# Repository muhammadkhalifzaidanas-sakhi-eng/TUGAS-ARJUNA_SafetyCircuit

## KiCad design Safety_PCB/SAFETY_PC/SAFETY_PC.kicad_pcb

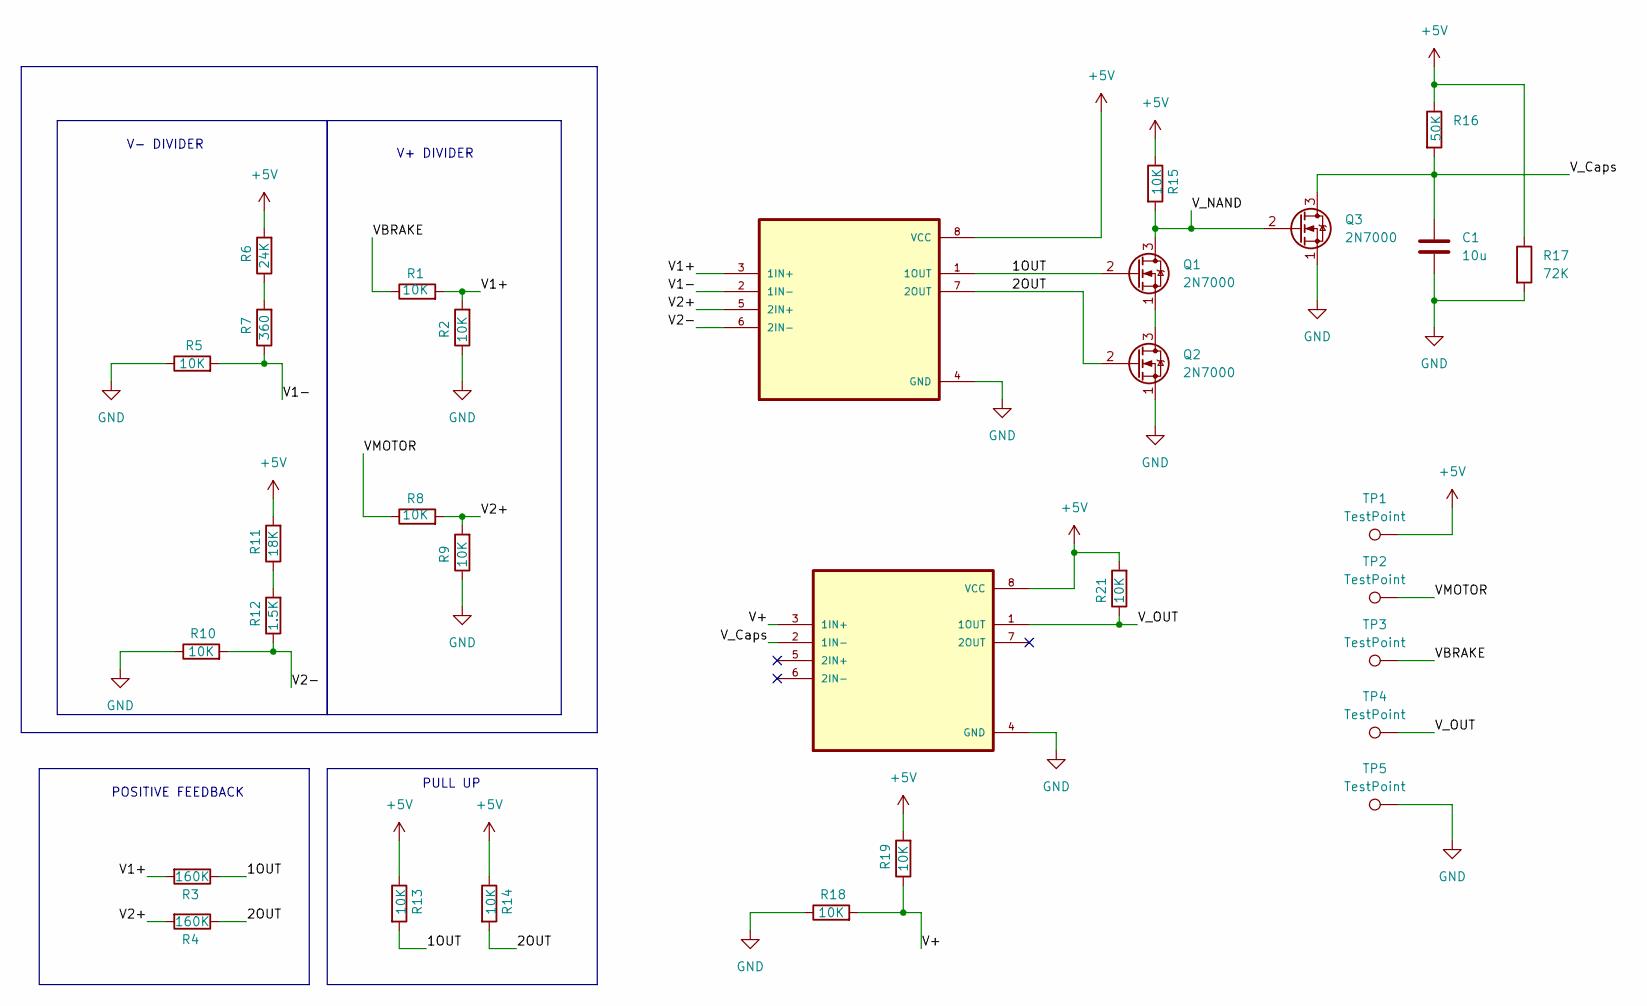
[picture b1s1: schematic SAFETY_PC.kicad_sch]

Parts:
C1: 10u; C_0603_1608Metric
Q1, Q2, Q3: 2N7000; TO-92_Inline_Horizontal1
R1, R2, R5, R8, R9, R10, R13, R14, R15, R18, R19, R21: 10K; R_0603_1608Metric
R3, R4: 160K; R_0603_1608Metric
R6: 24K; R_0603_1608Metric
R7: 360; R_0603_1608Metric
R11: 18K; R_0603_1608Metric
R12: 1.5K; R_0603_1608Metric
R16: 50K; R_0603_1608Metric
R17: 72K; R_0603_1608Metric
TP1, TP2, TP3, TP4, TP5: TestPoint; TestPoint_THTPad_D2.5mm_Drill1.2mm
U1, U2: LM393P; DIP794W45P254L959H508Q8

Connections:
+5V: R6.2, R11.2, R13.1, R14.1, R15.1, R16.1, R17.1, R19.2, R21.2, TP1.1, U1.8 (VCC), U2.8 (VCC)
/1OUT: Q1.2 (G), R3.1, R13.2, U1.1 (1OUT)
/2OUT: Q2.2 (G), R4.1, R14.2, U1.7 (2OUT)
/V1+: R1.2, R2.2, R3.2, U1.3 (1IN+)
/V1-: R5.2, R7.1, U1.2 (1IN-)
/V2+: R4.2, R8.2, R9.2, U1.5 (2IN+)
/V2-: R10.2, R12.1, U1.6 (2IN-)
/V+: R18.2, R19.1, U2.3 (1IN+)
/VBRAKE: R1.1, TP3.1
/VMOTOR: R8.1, TP2.1
/V_Caps: C1.1, Q3.3 (D), R16.2, U2.2 (1IN-)
/V_NAND: Q1.3 (D), Q3.2 (G), R15.2
/V_OUT: R21.1, TP4.1, U2.1 (1OUT)
GND: C1.2, Q2.1 (S), Q3.1 (S), R2.1, R5.1, R9.1, R10.1, R17.2, R18.1, TP5.1, U1.4 (GND), U2.4 (GND)
unnamed: Q1.1 (S), Q2.3 (D)
unnamed: R6.1, R7.2
unnamed: R11.1, R12.2

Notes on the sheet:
V+ DIVIDER
V- DIVIDER
POSITIVE FEEDBACK
PULL UP

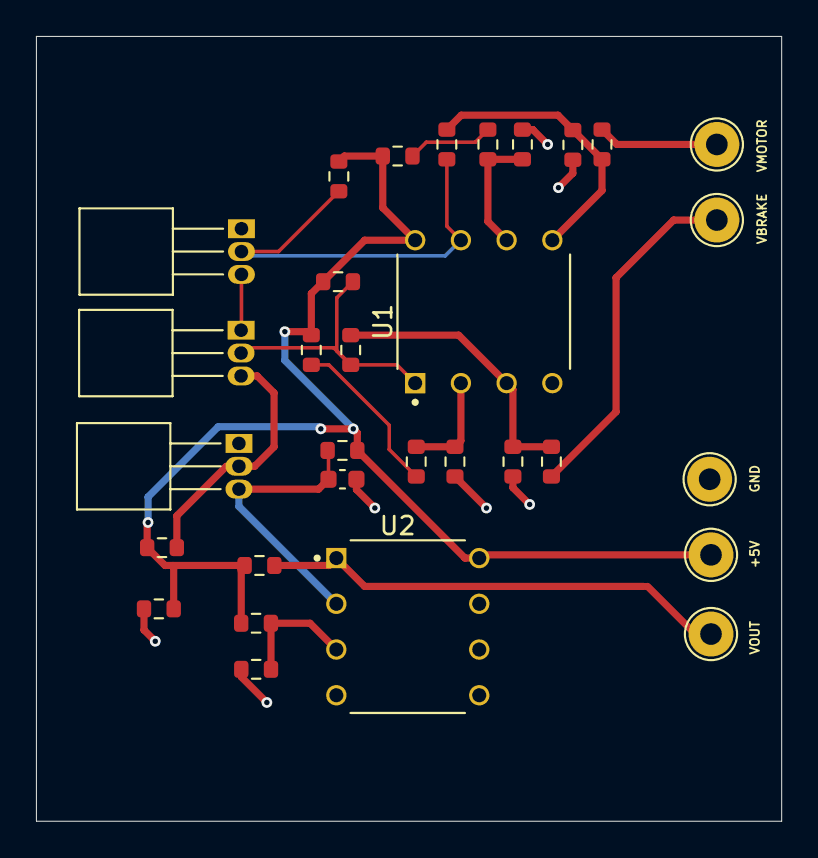
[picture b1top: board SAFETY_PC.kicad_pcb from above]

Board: 2 copper layers, 41.4 x 43.6 mm, 31 parts (0 on the bottom side), 17 nets.

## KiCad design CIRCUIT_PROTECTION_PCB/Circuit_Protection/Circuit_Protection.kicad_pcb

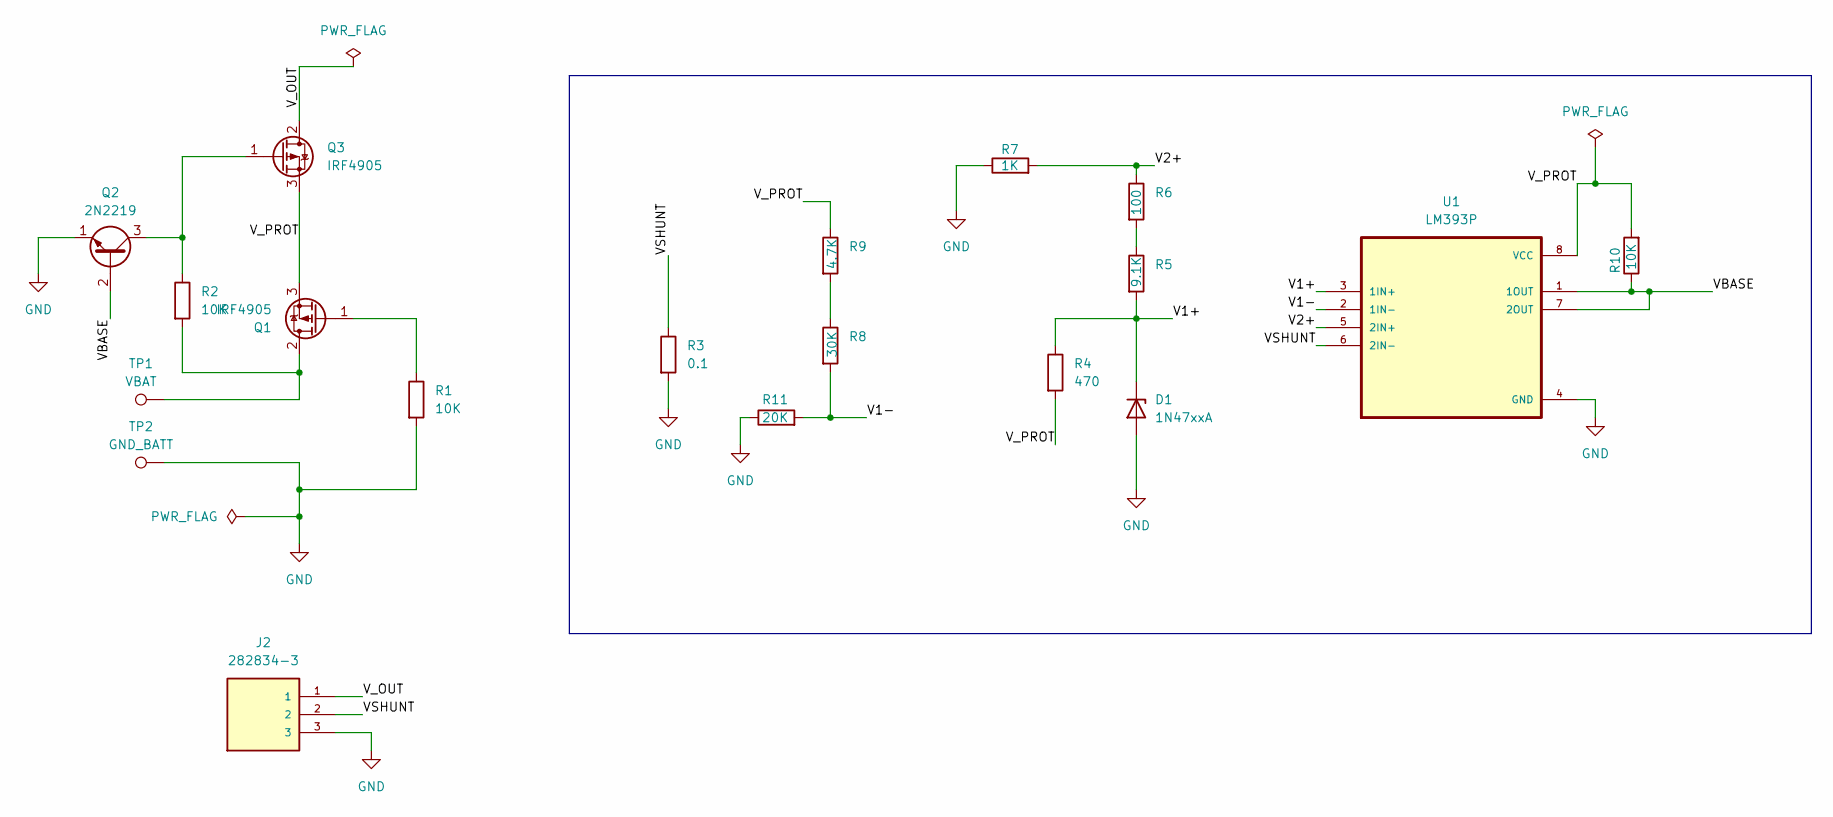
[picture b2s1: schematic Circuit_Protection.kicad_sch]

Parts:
D1: 1N47xxA; D_DO-41_SOD81_P10.16mm_Horizontal
J2: 282834-3; TE_282834-3; PARTREV D
Q1, Q3: IRF4905; TO-220-3_Horizontal_TabUp
Q2: 2N2219; TO-39-3
R1, R2, R10: 10K; R_0603_1608Metric
R3: 0.1; R_2512_6332Metric
R4: 470; R_0603_1608Metric
R5: 9.1K; R_0603_1608Metric
R6: 100; R_0603_1608Metric
R7: 1K; R_0603_1608Metric
R8: 30K; R_0603_1608Metric
R9: 4.7K; R_0603_1608Metric
R11: 20K; R_0603_1608Metric
TP1: VBAT; TestPoint_THTPad_D2.5mm_Drill1.2mm
TP2: GND_BATT; TestPoint_THTPad_2.5x2.5mm_Drill1.2mm
U1: LM393P; DIP794W45P254L959H508Q8

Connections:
/V1+: D1.1 (K), R4.1, R5.2, U1.3 (1IN+)
/V1-: R8.2, R11.2, U1.2 (1IN-)
/V2+: R6.1, R7.2, U1.5 (2IN+)
/VBASE: Q2.2 (B), R10.1, U1.1 (1OUT), U1.7 (2OUT)
/VSHUNT: J2.2, R3.1, U1.6 (2IN-)
/V_OUT: J2.1, Q3.2 (D)
/V_PROT: Q1.3 (S), Q3.3 (S), R4.2, R9.1, R10.2, U1.8 (VCC)
GND: D1.2 (A), J2.3, Q2.1 (E), R1.2, R3.2, R7.1, R11.1, TP2.1, U1.4 (GND)
unnamed: Q1.2 (D), R2.2, TP1.1
unnamed: Q1.1 (G), R1.1
unnamed: Q2.3 (C), Q3.1 (G), R2.1
unnamed: R5.1, R6.2
unnamed: R8.1, R9.2

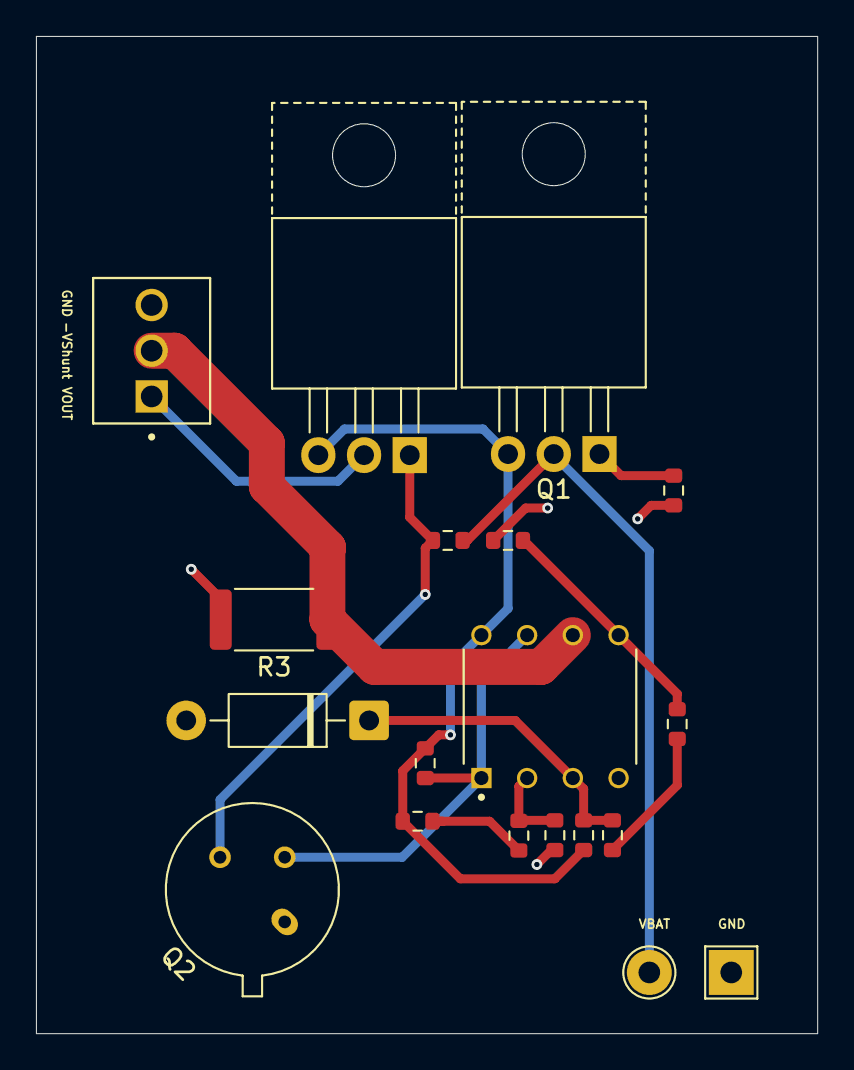
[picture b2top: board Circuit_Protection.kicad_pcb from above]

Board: 2 copper layers, 43.4 x 55.4 mm, 19 parts (0 on the bottom side), 13 nets.
